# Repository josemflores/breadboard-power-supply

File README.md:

# Breadboard Power Supply

A dual-output regulated power supply PCB designed to sit across a breadboard and provide selectable **3.3V and 5V** rails. Built as a learning project using KiCad.

---

## Specifications

| Parameter | Value |
|---|---|
| Input Voltage | 12V DC (barrel jack) |
| Output Voltages | 3.3V / 5V (selectable per rail) |
| 5V Regulator | LM7805 (TO-220) |
| 3.3V Regulator | LM317 (TO-220) |
| Output Connectors | 2.54mm pin headers + screw terminals |
| Board Revision | V0.1 |

---

## Schematic

The design is split into three sections:

- **Input and 5V circuit** — 12V enters through a barrel jack with an EG1218 slide switch. The LM7805 regulates it down to 5V with 10µF and 0.1µF decoupling caps.
- **3.3V circuit** — The LM317 is configured with an R1=330Ω, R2=330Ω, R3=560Ω resistor network to output 3.3V. A power indicator LED is included on the input rail.
- **Output and switches** — Each side of the board (top and bottom breadboard rails) has a 3-pin voltage selector header (3.3V or 5V), a 2-pin breadboard connector, and a screw terminal for jumper wire output.

---

## PCB Layout

---

## 3D Render

---

## Features

- Dual independent output rails — each side of the breadboard gets its own voltage selector
- Selectable 3.3V or 5V per rail via jumper header
- Power indicator LED on input
- Screw terminal outputs for jumper wire connections
- Compact form factor sized to straddle a standard breadboard

---

## Tools Used

- KiCad EDA 10.0.1
- KiCad built-in symbol and footprint libraries

---

## Design Notes

This was my first complete PCB layout from schematic to fabrication-ready files. A few things I paid attention to:

- The LM317 output voltage is set by the ratio of R2 and R3 (330Ω / 560Ω), following the standard adjust-pin formula: V_out = 1.25 × (1 + R2/R1)
- Decoupling capacitors are placed close to regulator output pins to suppress noise
- The screw terminals are flipped vertically so that pin 1 is GND (arranged below pin 2) for intuitive polarity

---

## Acknowledgements

Designed alongside a tutorial as an introduction to KiCad PCB design and linear voltage regulators.

---

*Jose Perez Flores — 2026*

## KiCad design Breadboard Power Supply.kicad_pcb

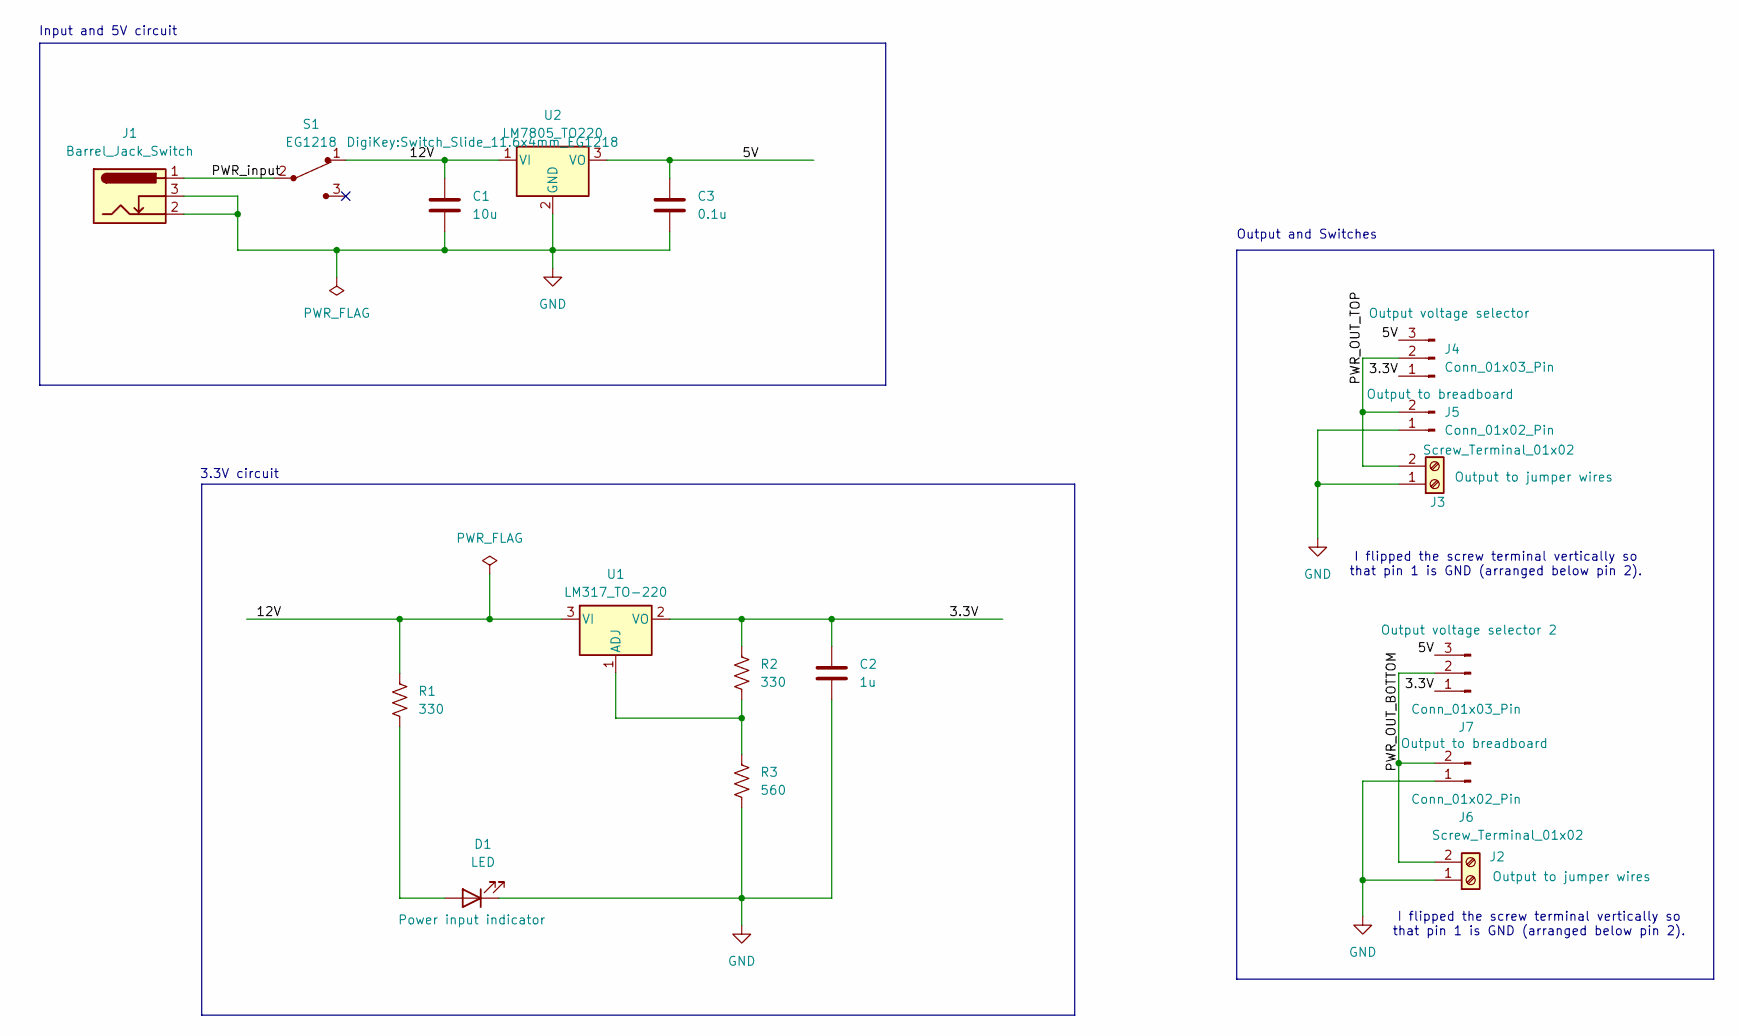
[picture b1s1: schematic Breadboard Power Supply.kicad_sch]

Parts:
C1: 10u; C_Disc_D3.0mm_W1.6mm_P2.50mm
C2: 1u; C_Disc_D3.0mm_W1.6mm_P2.50mm
C3: 0.1u; C_Disc_D3.0mm_W1.6mm_P2.50mm
D1: LED; LED_D5.0mm
J1: Barrel_Jack_Switch; BarrelJack_Horizontal
J2, J3: Screw_Terminal_01x02; TerminalBlock_bornier-2_P5.08mm
J4, J7: Conn_01x03_Pin; PinHeader_1x03_P2.54mm_Vertical
J5, J6: Conn_01x02_Pin; PinHeader_1x02_P2.54mm_Vertical
R1, R2: 330; R_Axial_DIN0204_L3.6mm_D1.6mm_P7.62mm_Horizontal
R3: 560; R_Axial_DIN0204_L3.6mm_D1.6mm_P7.62mm_Horizontal
S1: EG1218; Switch_Slide_11.6x4mm_EG1218; MPN EG1218
U1: LM317_TO-220; TO-220-3_Vertical
U2: LM7805_TO220; TO-220-3_Vertical

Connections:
/3.3V: C2.1, J4.1, J7.1, R2.2, U1.2 (VO)
/5V: C3.1, J4.3, J7.3, U2.3 (VO)
/12V: C1.1, R1.2, S1.1, U1.3 (VI), U2.1 (VI)
/PWR_OUT_BOTTOM: J2.2, J6.2, J7.2
/PWR_OUT_TOP: J3.2, J4.2, J5.2
/PWR_input: J1.1, S1.2
GND: C1.2, C2.2, C3.2, D1.1 (K), J1.2, J1.3, J2.1, J3.1, J5.1, J6.1, R3.1, U2.2 (GND)
unnamed: D1.2 (A), R1.1
unnamed: R2.1, R3.2, U1.1 (ADJ)

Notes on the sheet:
3.3V circuit
Output and Switches
I flipped the screw terminal vertically so that pin 1 is GND (arranged below pin 2).
Input and 5V circuit

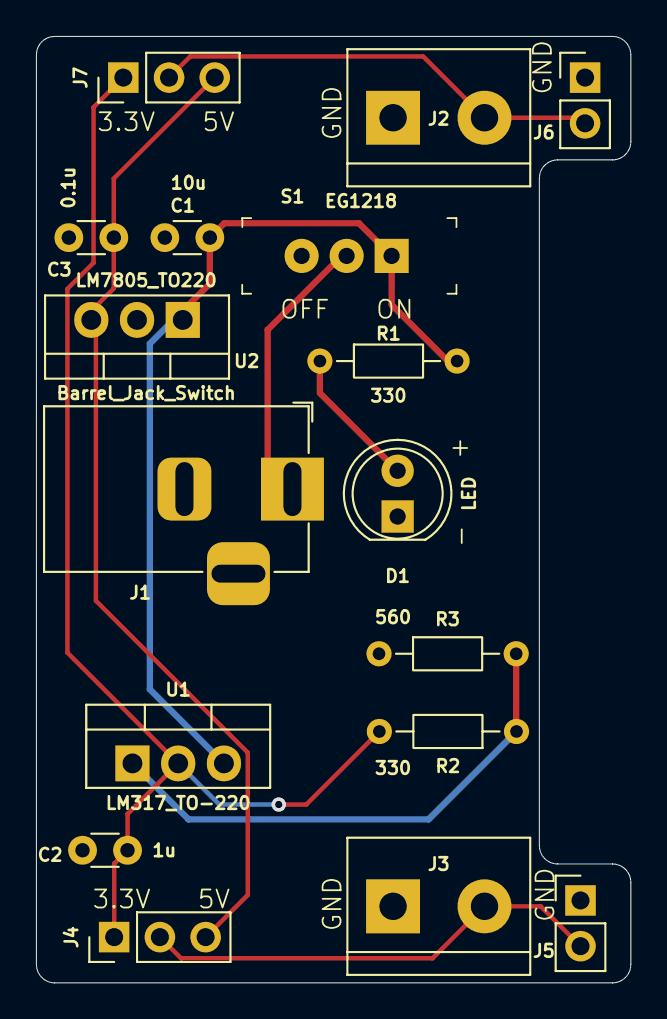
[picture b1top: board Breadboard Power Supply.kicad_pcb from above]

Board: 2 copper layers, 33.0 x 52.6 mm, 17 parts (0 on the bottom side), 9 nets.

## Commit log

2026-05-08 Initial commit: Breadboard Power Supply PCB and Schematic
2026-05-08 Added images
2026-05-08 Revise README for Breadboard Power Supply project
    Updated README to provide detailed specifications, schematic, PCB layout, and features of the Breadboard Power Supply project.
